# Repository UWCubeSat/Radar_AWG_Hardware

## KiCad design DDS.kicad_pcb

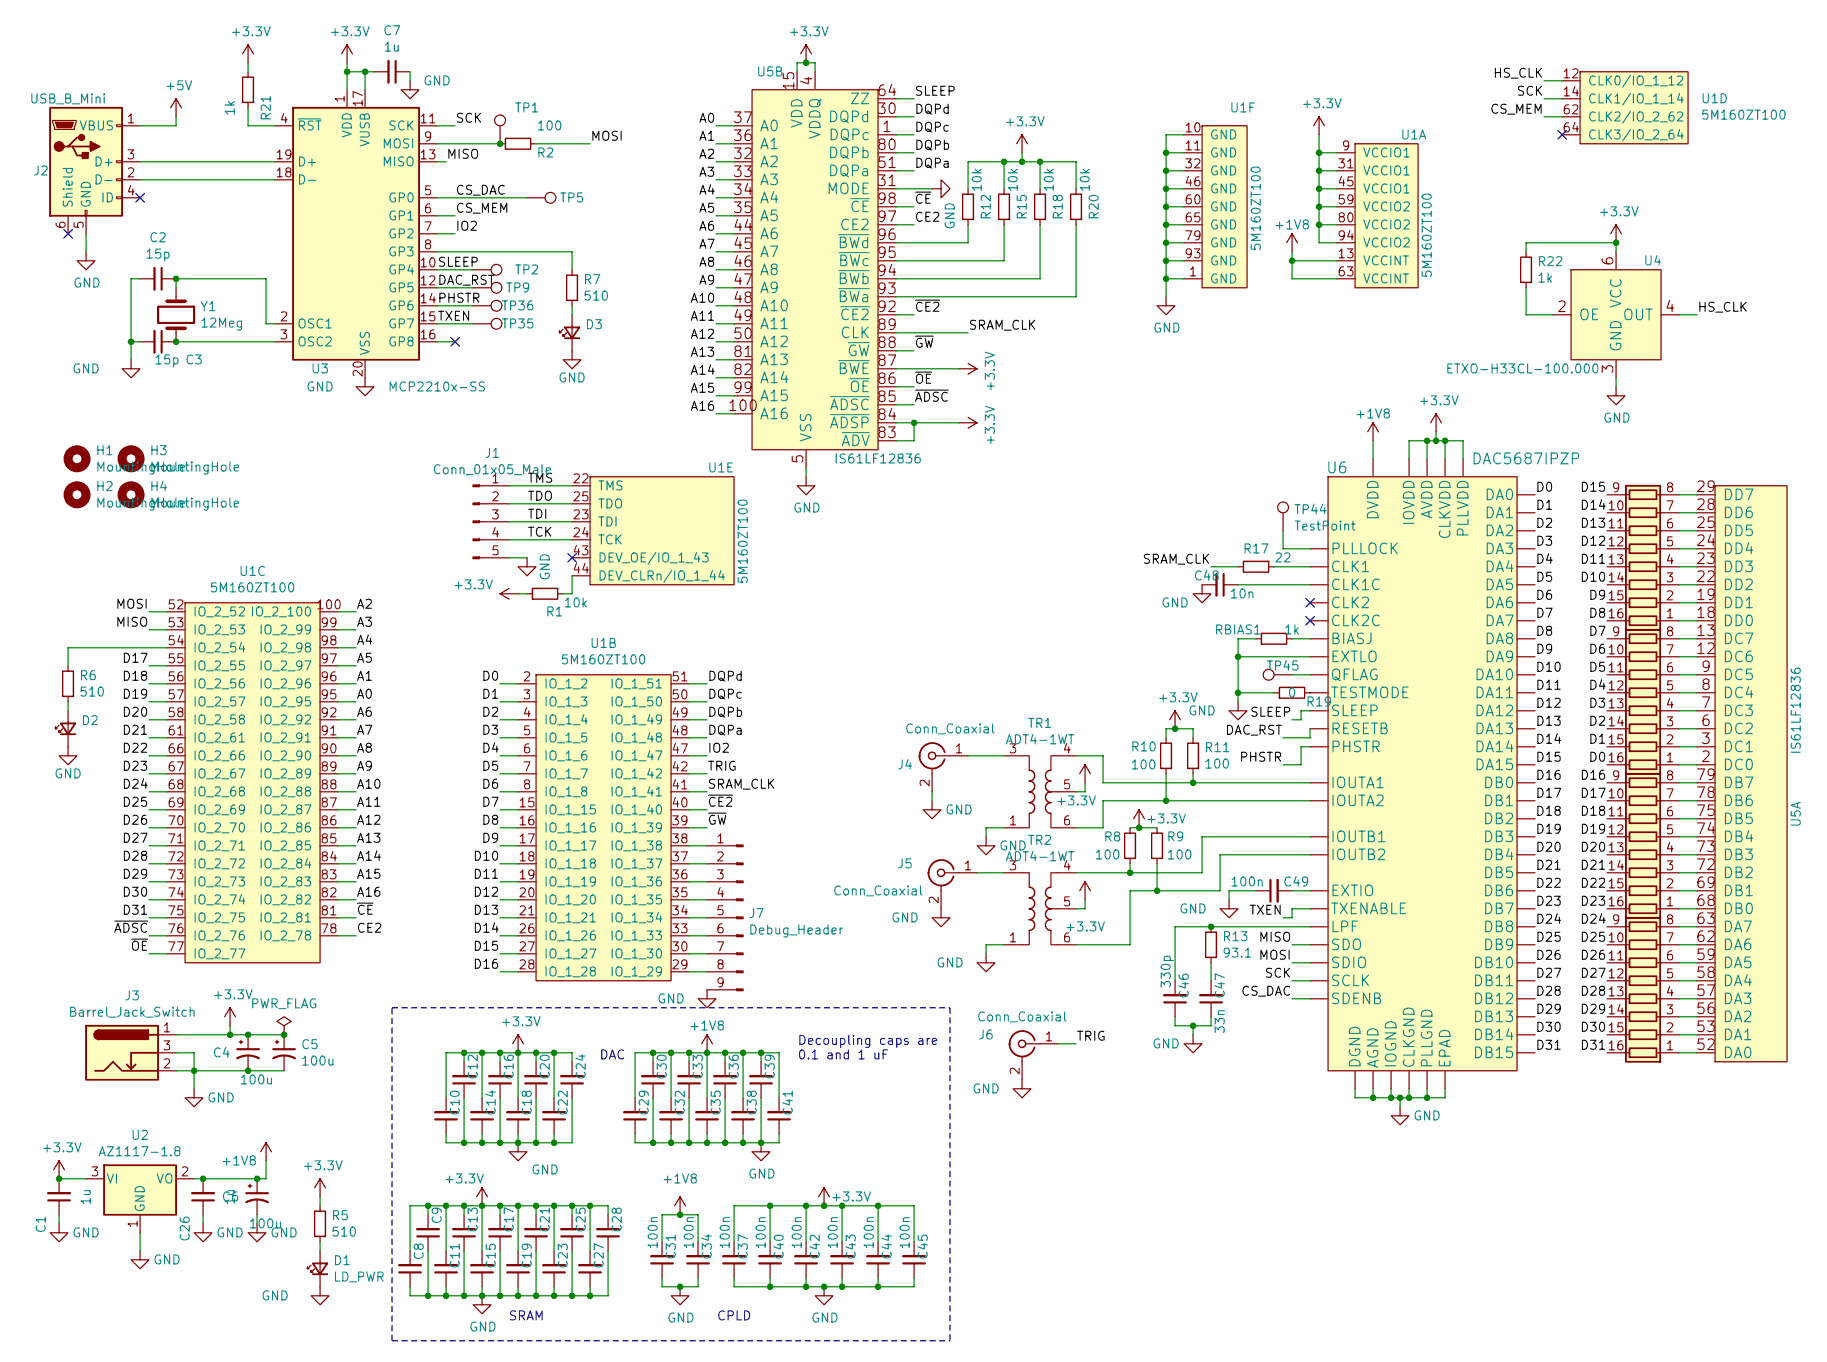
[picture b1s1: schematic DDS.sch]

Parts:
C1, C7, C9, C12, C13, C16, C17, C20, C21, C24, C25, C26, C28, C30, C33, C36, C39: 1u; C_0603_1608Metric
C2, C3: 15p; C_0603_1608Metric
C4, C5, C6: 100u; CP_Elec_6.3x3
C8, C10, C11, C14, C15, C18, C19, C22, C23, C27, C29, C31, C32, C34, C35, C37, C38, C40, C41, C42, C43, C44, C45, C49: 100n; C_0603_1608Metric
C46: 330p; C_0603_1608Metric
C47: 33n; C_0603_1608Metric
C48: 10n; C_0603_1608Metric
D1: LD_PWR; LED_0805_2012Metric
D2: LD_STATE; LED_0805_2012Metric
D3: LED_Small; LED_0805_2012Metric
H1, H2, H3, H4: MountingHole; MountingHole_3.2mm_M3
J1: Conn_01x05_Male; PinHeader_1x05_P2.54mm_Vertical
J2: USB_B_Mini; USB_Mini-B_Wuerth_65100516121_Horizontal
J3: Barrel_Jack_Switch; PJ-075DH-SMT-TR
J4, J5, J6: Conn_Coaxial; SMA_Samtec_SMA-J-P-X-ST-EM1_EdgeMount
J7: Debug_Header; PinHeader_1x09_P2.54mm_Vertical
R1, R12, R15, R18, R20: 10k; R_0603_1608Metric
R2, R8, R9, R10, R11: 100; R_0603_1608Metric
R5, R6, R7: 510; R_0603_1608Metric
R13: 93.1; R_0603_1608Metric
R17: 22; R_0603_1608Metric
R19: 0; R_0603_1608Metric
R21, R22: 1k; R_0603_1608Metric
RBIAS1: 1k; R_0603_1608Metric
RN3, RN4, RN5, RN6: R_Pack08; CAY16-470J8LF
TP1, TP2, TP5, TP9, TP35, TP36, TP44, TP45: TestPoint; TestPoint_Pad_D1.0mm
TR1, TR2: ADT4-1WT; Mini-Circuits_CD542_H2.84mm
U1: 5M160ZT100; TQFP-100_14x14mm_P0.5mm
U2: AZ1117-1.8; SOT-223-3_TabPin2
U3: MCP2210x-SS; SSOP-20_5.3x7.2mm_P0.65mm
U4: ETXO-H33CL-100.000; EXTO-H
U5: IS61LF12836; PQFP-100_14x20mm_P0.65mm
U6: DAC5687IPZP; TQFP-100-1EP_14x14mm_P0.5mm_EP5x5mm_ThermalVias
Y1: 12Meg; Crystal_SMD_HC49-SD_HandSoldering

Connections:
+1V8: C6.1, C26.2, C29.2, C30.2, C31.2, C32.2, C33.2, C34.2, C35.2, C36.2, C38.2, C39.2, C41.2, U1.13 (VCCINT), U1.63 (VCCINT), U2.2 (VO), U6.26 (DVDD), U6.32 (DVDD), U6.37 (DVDD), U6.44 (DVDD), U6.56 (DVDD), U6.68 (DVDD), U6.82 (DVDD), U6.89 (DVDD), U6.100 (DVDD)
+3V3: C1.2, C4.1, C5.1, C7.2, C8.2, C9.2, C10.2, C11.2, C12.2, C13.2, C14.2, C15.2, C16.2, C17.2, C18.2, C19.2, C20.2, C21.2, C22.2, C23.2, C24.2, C25.2, C27.2, C28.2, C37.2, C40.2, C42.2, C43.2, C44.2, C45.2, J3.1, R1.1, R5.2, R8.2, R9.2, R10.2, R11.2, R12.2, R15.2, R18.2, R20.2, R21.2, R22.2, TR1.5, TR2.5, U1.9 (VCCIO1), U1.31 (VCCIO1), U1.45 (VCCIO1), U1.59 (VCCIO2), U1.80 (VCCIO2), U1.94 (VCCIO2), U2.3 (VI), U3.1 (VDD), U3.17 (VUSB), U4.6 (VCC), U5.4 (VDDQ), U5.11 (VDDQ), U5.15 (VDD), U5.20 (VDDQ), U5.27 (VDDQ), U5.41 (VDD), U5.54 (VDDQ), U5.61 (VDDQ), U5.65 (VDD), U5.70 (VDDQ), U5.77 (VDDQ), U5.83 (~ADV), U5.84 (~ADSP), U5.87 (~BWE), U5.91 (VDD), U6.2 (AVDD), U6.3 (AVDD), U6.8 (AVDD), U6.10 (AVDD), U6.14 (AVDD), U6.16 (AVDD), U6.18 (AVDD), U6.23 (AVDD), U6.24 (AVDD), U6.46 (IOVDD), U6.61 (CLKVDD), U6.67 (PLLVDD), U6.80 (IOVDD)
/A0: U1.95 (IO_2_95), U5.37 (A0)
/A1: U1.96 (IO_2_96), U5.36 (A1)
/A2: U1.100 (IO_2_100), U5.32 (A2)
/A3: U1.99 (IO_2_99), U5.33 (A3)
/A4: U1.98 (IO_2_98), U5.34 (A4)
/A5: U1.97 (IO_2_97), U5.35 (A5)
/A6: U1.92 (IO_2_92), U5.44 (A6)
/A7: U1.91 (IO_2_91), U5.45 (A7)
/A8: U1.90 (IO_2_90), U5.46 (A8)
/A9: U1.89 (IO_2_89), U5.47 (A9)
/A10: U1.88 (IO_2_88), U5.48 (A10)
/A11: U1.87 (IO_2_87), U5.49 (A11)
/A12: U1.86 (IO_2_86), U5.50 (A12)
/A13: U1.85 (IO_2_85), U5.81 (A13)
/A14: U1.84 (IO_2_84), U5.82 (A14)
/A15: U1.83 (IO_2_83), U5.99 (A15)
/A16: U1.82 (IO_2_82), U5.100 (A16)
/CE2: U1.78 (IO_2_78), U5.97 (CE2)
/CS_DAC: TP5.1, U3.5 (GP0), U6.28 (SDENB)
/CS_MEM: U1.62 (CLK2/IO_2_62), U3.6 (GP1)
/D0: RN4.16 (R1.2), U1.2 (IO_1_2), U6.55 (DA0)
/D1: RN4.15 (R2.2), U1.3 (IO_1_3), U6.54 (DA1)
/D2: RN4.14 (R3.2), U1.4 (IO_1_4), U6.53 (DA2)
/D3: RN4.13 (R4.2), U1.5 (IO_1_5), U6.52 (DA3)
/D4: RN4.12 (R5.2), U1.6 (IO_1_6), U6.51 (DA4)
/D5: RN4.11 (R6.2), U1.7 (IO_1_7), U6.50 (DA5)
/D6: RN4.10 (R7.2), U1.8 (IO_1_8), U6.49 (DA6)
/D7: RN4.9 (R8.2), U1.15 (IO_1_15), U6.48 (DA7)
/D8: RN3.16 (R1.2), U1.16 (IO_1_16), U6.43 (DA8)
/D9: RN3.15 (R2.2), U1.17 (IO_1_17), U6.42 (DA9)
/D10: RN3.14 (R3.2), U1.18 (IO_1_18), U6.41 (DA10)
/D11: RN3.13 (R4.2), U1.19 (IO_1_19), U6.40 (DA11)
/D12: RN3.12 (R5.2), U1.20 (IO_1_20), U6.39 (DA12)
/D13: RN3.11 (R6.2), U1.21 (IO_1_21), U6.36 (DA13)
/D14: RN3.10 (R7.2), U1.26 (IO_1_26), U6.35 (DA14)
/D15: RN3.9 (R8.2), U1.27 (IO_1_27), U6.34 (DA15)
/D16: RN5.9 (R8.2), U1.28 (IO_1_28), U6.71 (DB0)
/D17: RN5.10 (R7.2), U1.55 (IO_2_55), U6.72 (DB1)
/D18: RN5.11 (R6.2), U1.56 (IO_2_56), U6.73 (DB2)
/D19: RN5.12 (R5.2), U1.57 (IO_2_57), U6.74 (DB3)
/D20: RN5.13 (R4.2), U1.58 (IO_2_58), U6.75 (DB4)
/D21: RN5.14 (R3.2), U1.61 (IO_2_61), U6.76 (DB5)
/D22: RN5.15 (R2.2), U1.66 (IO_2_66), U6.77 (DB6)
/D23: RN5.16 (R1.2), U1.67 (IO_2_67), U6.78 (DB7)
/D24: RN6.9 (R8.2), U1.68 (IO_2_68), U6.83 (DB8)
/D25: RN6.10 (R7.2), U1.69 (IO_2_69), U6.84 (DB9)
/D26: RN6.11 (R6.2), U1.70 (IO_2_70), U6.85 (DB10)
/D27: RN6.12 (R5.2), U1.71 (IO_2_71), U6.86 (DB11)
/D28: RN6.13 (R4.2), U1.72 (IO_2_72), U6.87 (DB12)
/D29: RN6.14 (R3.2), U1.73 (IO_2_73), U6.90 (DB13)
/D30: RN6.15 (R2.2), U1.74 (IO_2_74), U6.91 (DB14)
/D31: RN6.16 (R1.2), U1.75 (IO_2_75), U6.92 (DB15)
/DAC_RST: TP9.1, U3.12 (GP5), U6.95 (RESETB)
/DQPa: U1.48 (IO_1_48), U5.51 (DQPa)
/DQPb: U1.49 (IO_1_49), U5.80 (DQPb)
/DQPc: U1.50 (IO_1_50), U5.1 (DQPc)
/DQPd: U1.51 (IO_1_51), U5.30 (DQPd)
/HS_CLK: U1.12 (CLK0/IO_1_12), U4.4 (OUT)
/IO2: U1.47 (IO_1_47), U3.7 (GP2)
/MISO: U1.53 (IO_2_53), U3.13 (MISO), U6.31 (SDO)
/MOSI: R2.2, U1.52 (IO_2_52), U6.30 (SDIO)
/PHSTR: TP36.1, U3.14 (GP6), U6.94 (PHSTR)
/SCK: U1.14 (CLK1/IO_1_14), U3.11 (SCK), U6.29 (SCLK)
/SLEEP: TP2.1, U3.10 (GP4), U5.64 (ZZ), U6.96 (SLEEP)
/SRAM_CLK: R17.2, U1.41 (IO_1_41), U5.89 (CLK)
/TCK: J1.4, U1.24 (TCK)
/TDI: J1.3, U1.23 (TDI)
/TDO: J1.2, U1.25 (TDO)
/TMS: J1.1, U1.22 (TMS)
/TRIG: J6.1 (In), U1.42 (IO_1_42)
/TXEN: TP35.1, U3.15 (GP7), U6.33 (TXENABLE)
/~ADSC: U1.76 (IO_2_76), U5.85 (~ADSC)
/~CE: U1.81 (IO_2_81), U5.98 (~CE)
/~CE2: U1.40 (IO_1_40), U5.92 (~CE2)
/~GW: U1.39 (IO_1_39), U5.88 (~GW)
/~OE: U1.77 (IO_2_77), U5.86 (~OE)
AGND: C1.1, C2.2, C3.2, C4.2, C5.2, C6.2, C7.1, C8.1, C9.1, C10.1, C11.1, C12.1, C13.1, C14.1, C15.1, C16.1, C17.1, C18.1, C19.1, C20.1, C21.1, C22.1, C23.1, C24.1, C25.1, C26.1, C27.1, C28.1, C29.1, C30.1, C31.1, C32.1, C33.1, C34.1, C35.1, C36.1, C37.1, C38.1, C39.1, C40.1, C41.1, C42.1, C43.1, C44.1, C45.1, C46.1, C47.1, C48.2, C49.1, D1.1 (K), D2.1 (K), D3.1 (K), J1.5, J2.5 (GND), J3.2, J3.3, J4.2 (Ext), J5.2 (Ext), J6.2 (Ext), J7.9, R19.1, RBIAS1.1, TR1.1, TR2.1, U1.1 (GND), U1.10 (GND), U1.11 (GND), U1.32 (GND), U1.46 (GND), U1.60 (GND), U1.65 (GND), U1.79 (GND), U1.93 (GND), U2.1 (GND), U3.20 (VSS), U4.3 (GND), U5.5 (VSS), U5.10 (VSS), U5.17 (VSS), U5.21 (VSS), U5.26 (VSS), U5.31 (MODE), U5.40 (VSS), U5.55 (VSS), U5.60 (VSS), U5.67 (VSS), U5.71 (VSS), U5.76 (VSS), U5.90 (VSS), U6.1 (AGND), U6.4 (AGND), U6.7 (AGND), U6.9 (AGND), U6.12 (AGND), U6.15 (EXTLO), U6.17 (AGND), U6.19 (AGND), U6.22 (AGND), U6.25 (AGND), U6.27 (DGND), U6.38 (DGND), U6.45 (DGND), U6.47 (IOGND), U6.57 (DGND), U6.58 (CLKGND), U6.64 (CLKGND), U6.65 (PLLGND), U6.69 (DGND), U6.79 (IOGND), U6.81 (DGND), U6.88 (DGND), U6.93 (DGND), U6.99 (DGND), U6.101 (EPAD)
unnamed: C2.1, U3.2 (OSC1), Y1.1
unnamed: C3.1, U3.3 (OSC2), Y1.2
unnamed: C46.2, R13.2, U6.66 (LPF)
unnamed: C47.2, R13.1
unnamed: C48.1, U6.60 (CLK1C)
unnamed: C49.2, U6.11 (EXTIO)
unnamed: D1.2 (A), R5.1
unnamed: D2.2 (A), R6.1
unnamed: D3.2 (A), R7.1
unnamed: J2.2 (D-), U3.18 (D-)
unnamed: J2.3 (D+), U3.19 (D+)
unnamed: J4.1 (In), TR1.3
unnamed: J5.1 (In), TR2.3
unnamed: J7.1, U1.38 (IO_1_38)
unnamed: J7.2, U1.37 (IO_1_37)
unnamed: J7.3, U1.36 (IO_1_36)
unnamed: J7.4, U1.35 (IO_1_35)
unnamed: J7.5, U1.34 (IO_1_34)
unnamed: J7.6, U1.33 (IO_1_33)
unnamed: J7.7, U1.30 (IO_1_30)
unnamed: J7.8, U1.29 (IO_1_29)
unnamed: R1.2, U1.44 (DEV_CLRn/IO_1_44)
unnamed: R2.1, TP1.1, U3.9 (MOSI)
unnamed: R6.2, U1.54 (IO_2_54)
unnamed: R7.2, U3.8 (GP3)
unnamed: R8.1, TR2.4, U6.5 (IOUTB1)
unnamed: R9.1, TR2.6, U6.6 (IOUTB2)
unnamed: R10.1, TR1.6, U6.20 (IOUTA2)
unnamed: R11.1, TR1.4, U6.21 (IOUTA1)
unnamed: R12.1, U5.96 (~BWd)
unnamed: R15.1, U5.95 (~BWc)
unnamed: R17.1, U6.59 (CLK1)
unnamed: R18.1, U5.94 (~BWb)
unnamed: R19.2, U6.97 (TESTMODE)
unnamed: R20.1, U5.93 (~BWa)
unnamed: R21.1, U3.4 (~RST)
unnamed: R22.1, U4.2 (OE)
unnamed: RBIAS1.2, U6.13 (BIASJ)
unnamed: RN3.1 (R1.1), U5.18 (DD0)
unnamed: RN3.2 (R2.1), U5.19 (DD1)
unnamed: RN3.3 (R3.1), U5.22 (DD2)
unnamed: RN3.4 (R4.1), U5.23 (DD3)
unnamed: RN3.5 (R5.1), U5.24 (DD4)
unnamed: RN3.6 (R6.1), U5.25 (DD5)
unnamed: RN3.7 (R7.1), U5.28 (DD6)
unnamed: RN3.8 (R8.1), U5.29 (DD7)
unnamed: RN4.1 (R1.1), U5.2 (DC0)
unnamed: RN4.2 (R2.1), U5.3 (DC1)
unnamed: RN4.3 (R3.1), U5.6 (DC2)
unnamed: RN4.4 (R4.1), U5.7 (DC3)
unnamed: RN4.5 (R5.1), U5.8 (DC4)
unnamed: RN4.6 (R6.1), U5.9 (DC5)
unnamed: RN4.7 (R7.1), U5.12 (DC6)
unnamed: RN4.8 (R8.1), U5.13 (DC7)
unnamed: RN5.1 (R1.1), U5.68 (DB0)
unnamed: RN5.2 (R2.1), U5.69 (DB1)
unnamed: RN5.3 (R3.1), U5.72 (DB2)
unnamed: RN5.4 (R4.1), U5.73 (DB3)
unnamed: RN5.5 (R5.1), U5.74 (DB4)
unnamed: RN5.6 (R6.1), U5.75 (DB5)
unnamed: RN5.7 (R7.1), U5.78 (DB6)
unnamed: RN5.8 (R8.1), U5.79 (DB7)
unnamed: RN6.1 (R1.1), U5.52 (DA0)
unnamed: RN6.2 (R2.1), U5.53 (DA1)
unnamed: RN6.3 (R3.1), U5.56 (DA2)
unnamed: RN6.4 (R4.1), U5.57 (DA3)
unnamed: RN6.5 (R5.1), U5.58 (DA4)
unnamed: RN6.6 (R6.1), U5.59 (DA5)
unnamed: RN6.7 (R7.1), U5.62 (DA6)
unnamed: RN6.8 (R8.1), U5.63 (DA7)
unnamed: TP44.1, U6.70 (PLLLOCK)
unnamed: TP45.1, U6.98 (QFLAG)

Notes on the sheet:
Decoupling caps are 0.1 and 1 uF
SRAM
DAC
CPLD

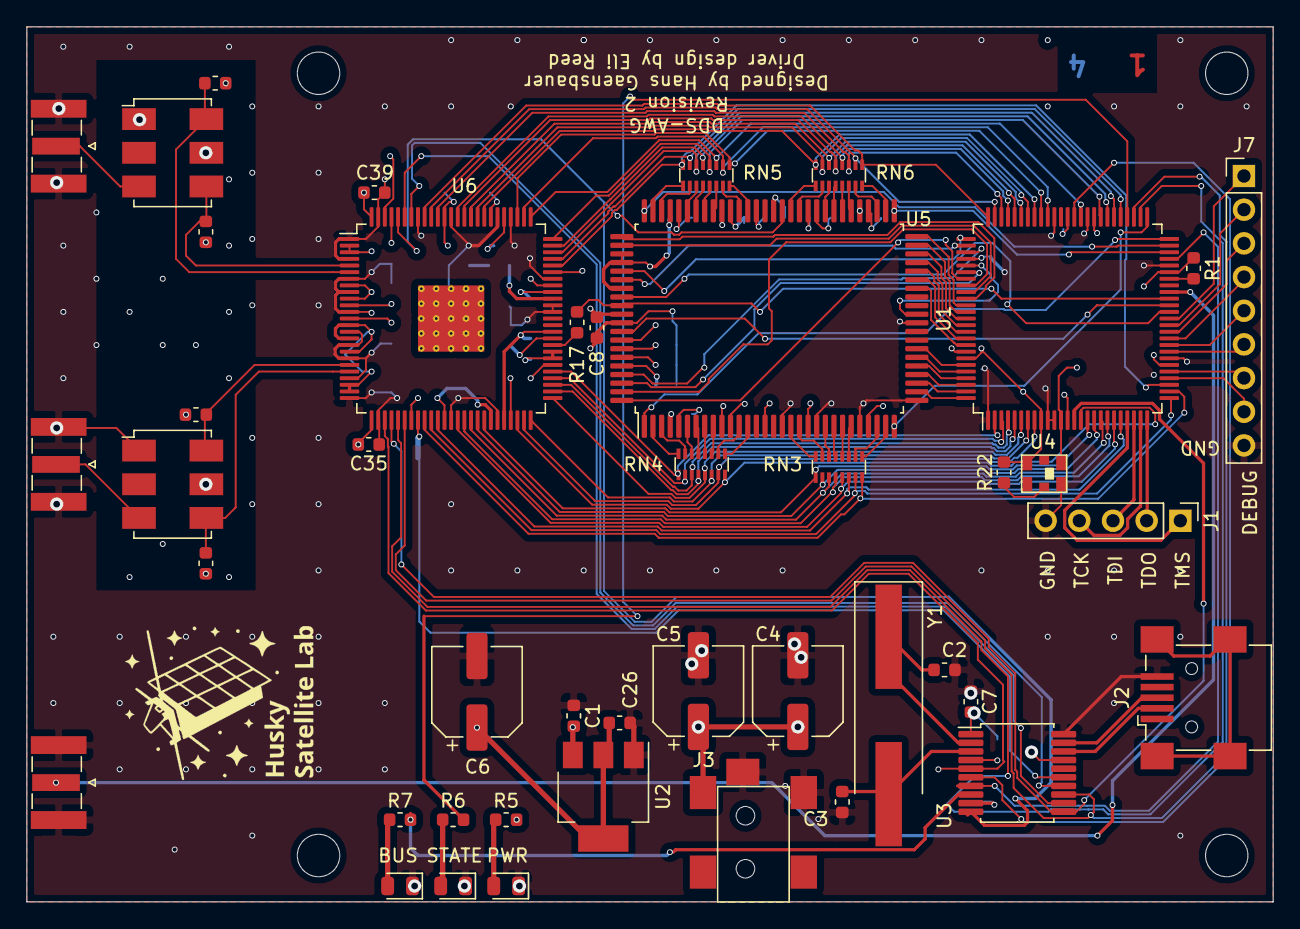
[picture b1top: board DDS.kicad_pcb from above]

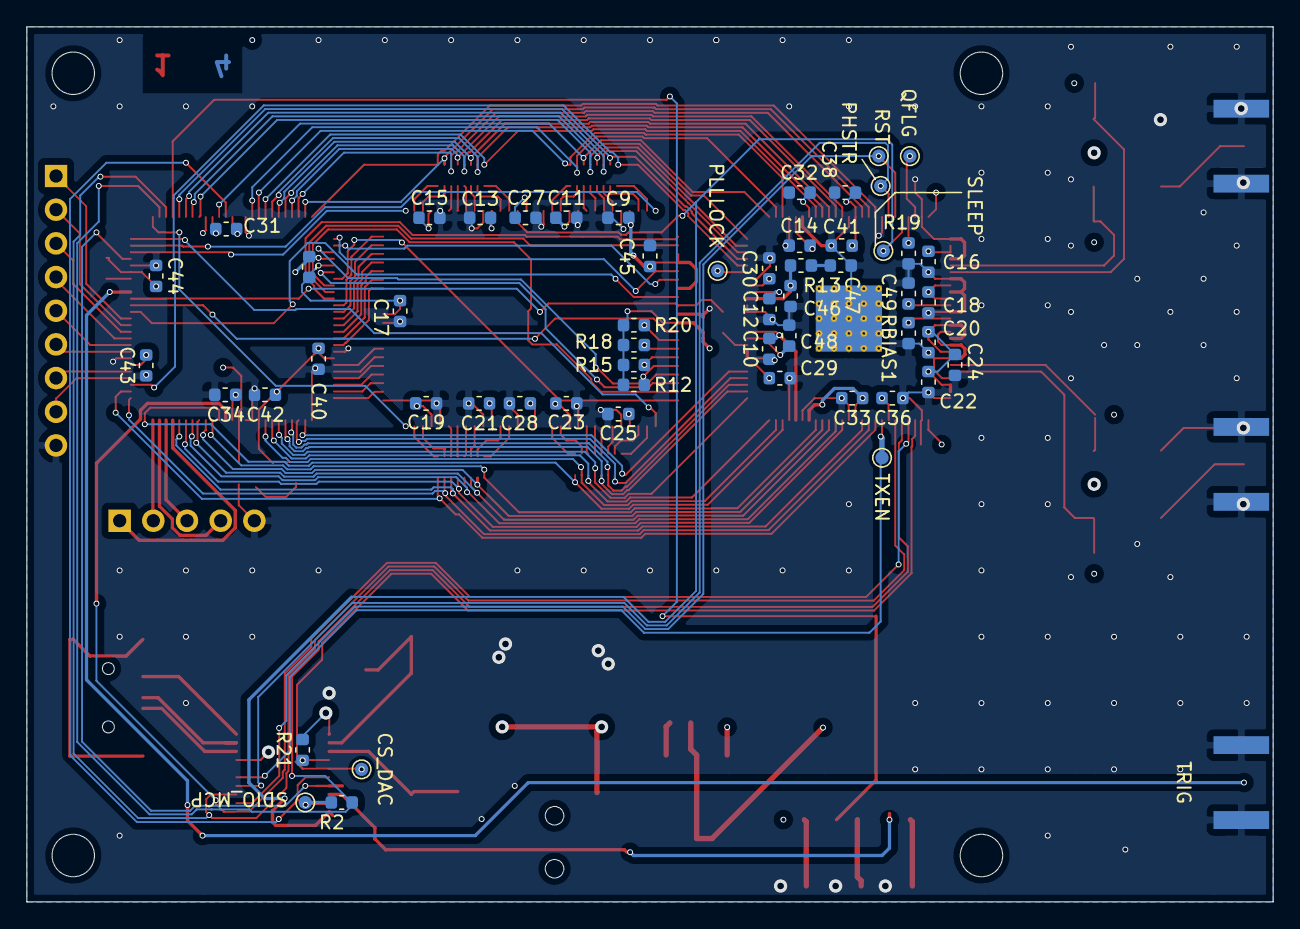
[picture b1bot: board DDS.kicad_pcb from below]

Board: 4 copper layers, 94.0 x 66.0 mm, 103 parts (55 on the bottom side), 151 nets.

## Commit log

2020-12-01 Added initial files
    Initial Commit
2021-05-23 new changes
